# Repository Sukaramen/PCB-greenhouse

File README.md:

# PCB-greenhouse
PCB greenhouse kampus merdeka

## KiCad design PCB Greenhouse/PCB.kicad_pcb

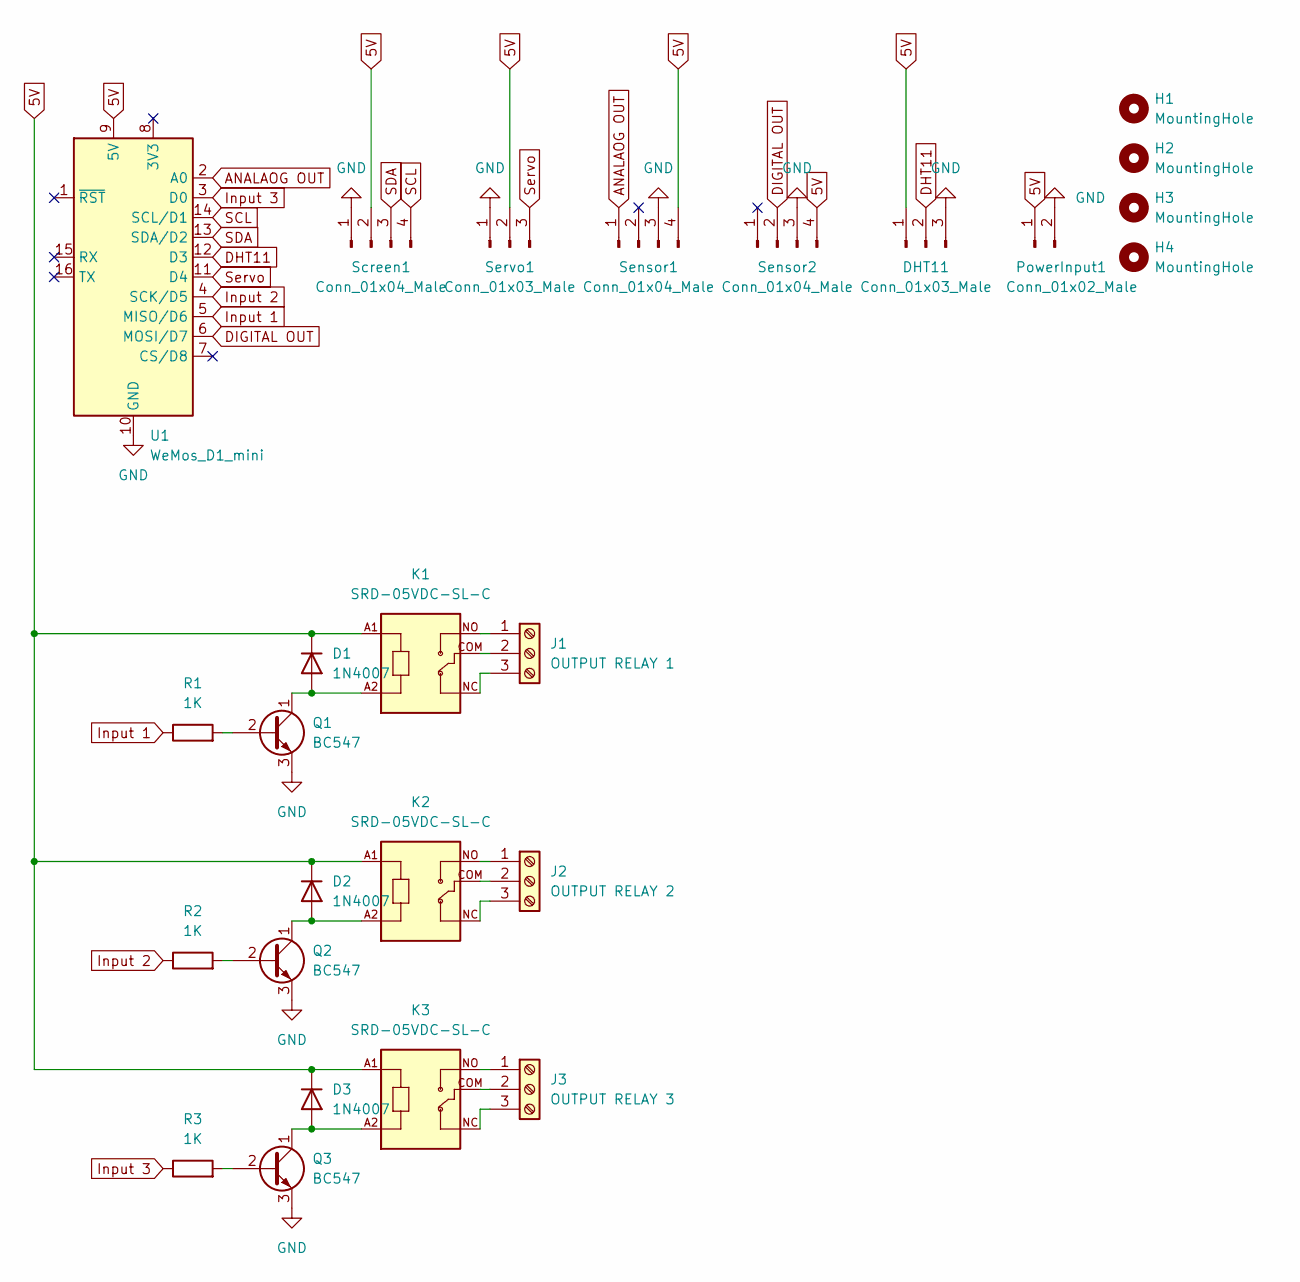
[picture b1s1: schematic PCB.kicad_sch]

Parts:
D1, D2, D3: 1N4007; D_DO-41_SOD81_P10.16mm_Horizontal
DHT11: Conn_01x03_Male; PinHeader_1x03_P2.54mm_Vertical
H1, H2, H3, H4: MountingHole; MountingHole_3.2mm_M3
J1: OUTPUT RELAY 1; TerminalBlock_Altech_AK300-3_P5.00mm
J2: OUTPUT RELAY 2; TerminalBlock_Altech_AK300-3_P5.00mm
J3: OUTPUT RELAY 3; TerminalBlock_Altech_AK300-3_P5.00mm
K1, K2, K3: SRD-05VDC-SL-C; RELAY_SRD-05VDC-SL-C
PowerInput1: Conn_01x02_Male; PinHeader_1x02_P2.54mm_Vertical
Q1, Q2, Q3: BC547; TO-92L_Inline_Wide
R1, R2, R3: 1K; R_Axial_DIN0207_L6.3mm_D2.5mm_P7.62mm_Horizontal
Screen1: Conn_01x04_Male; PinHeader_1x04_P2.54mm_Vertical
Sensor1, Sensor2: Conn_01x04_Male; PinHeader_1x04_P2.54mm_Vertical
Servo1: Conn_01x03_Male; PinHeader_1x03_P2.54mm_Vertical
U1: WeMos_D1_mini; WEMOS_D1_mini_light

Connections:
5V: D1.1 (K), D2.1 (K), D3.1 (K), DHT11.1, K1.A1, K2.A1, K3.A1, PowerInput1.1, Screen1.2, Sensor1.4, Sensor2.4, Servo1.2, U1.9 (5V)
ANALAOG OUT: Sensor1.1, U1.2 (A0)
DHT11: DHT11.2, U1.12 (D3)
DIGITAL OUT: Sensor2.2, U1.6 (MOSI/D7)
GND: DHT11.3, PowerInput1.2, Q1.3 (E), Q2.3 (E), Q3.3 (E), Screen1.1, Sensor1.3, Sensor2.3, Servo1.1, U1.10 (GND)
Input 1: R1.1, U1.5 (MISO/D6)
Input 2: R2.1, U1.4 (SCK/D5)
Input 3: R3.1, U1.3 (D0)
unnamed: D1.2 (A), K1.A2, Q1.1 (C)
unnamed: D2.2 (A), K2.A2, Q2.1 (C)
unnamed: D3.2 (A), K3.A2, Q3.1 (C)
unnamed: J1.1, K1.NO
unnamed: J1.2, K1.COM
unnamed: J1.3, K1.NC
unnamed: J2.1, K2.NO
unnamed: J2.2, K2.COM
unnamed: J2.3, K2.NC
unnamed: J3.1, K3.NO
unnamed: J3.2, K3.COM
unnamed: J3.3, K3.NC
unnamed: Q1.2 (B), R1.2
unnamed: Q2.2 (B), R2.2
unnamed: Q3.2 (B), R3.2
SCL: Screen1.4, U1.14 (SCL/D1)
SDA: Screen1.3, U1.13 (SDA/D2)
Servo: Servo1.3, U1.11 (D4)

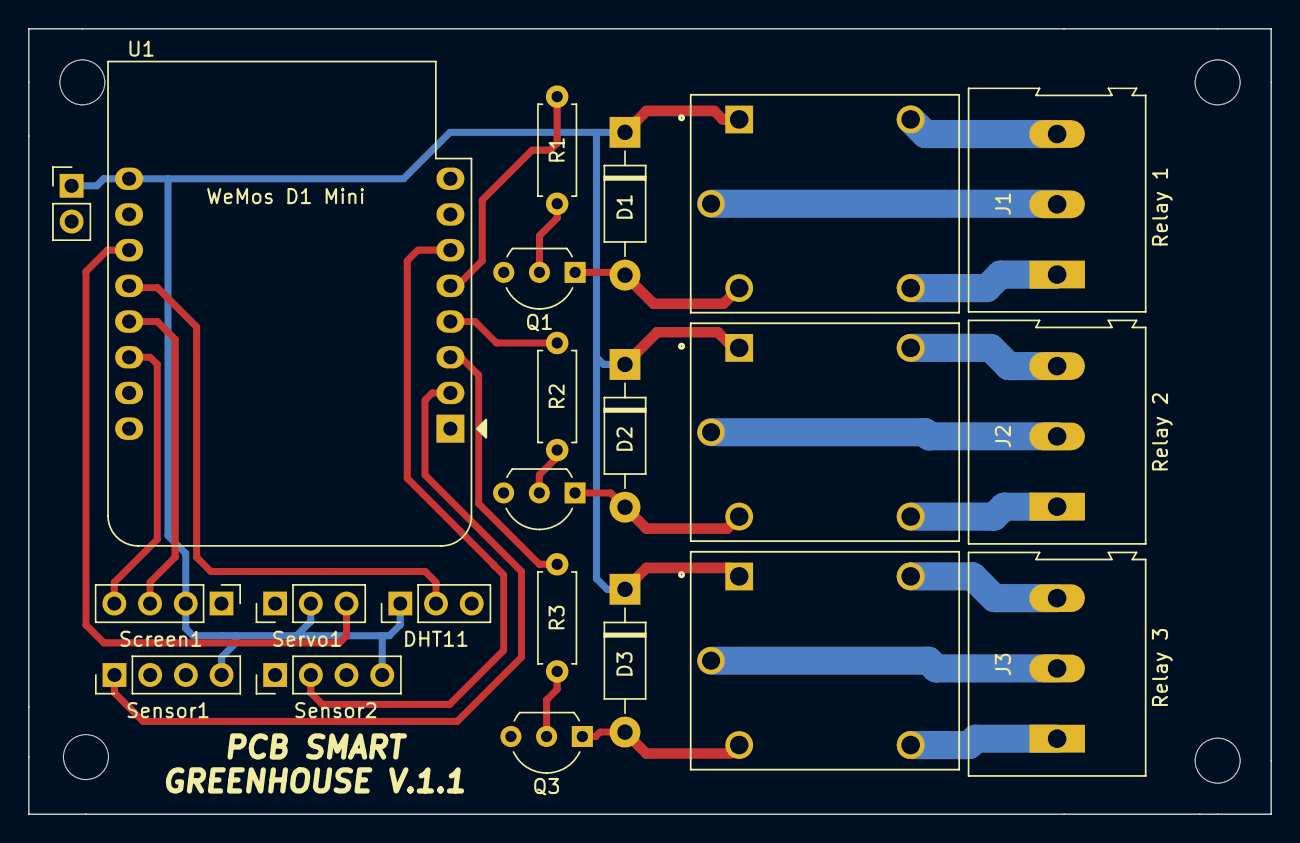
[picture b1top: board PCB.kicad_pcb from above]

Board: 2 copper layers, 88.4 x 55.9 mm, 26 parts (0 on the bottom side), 26 nets.
